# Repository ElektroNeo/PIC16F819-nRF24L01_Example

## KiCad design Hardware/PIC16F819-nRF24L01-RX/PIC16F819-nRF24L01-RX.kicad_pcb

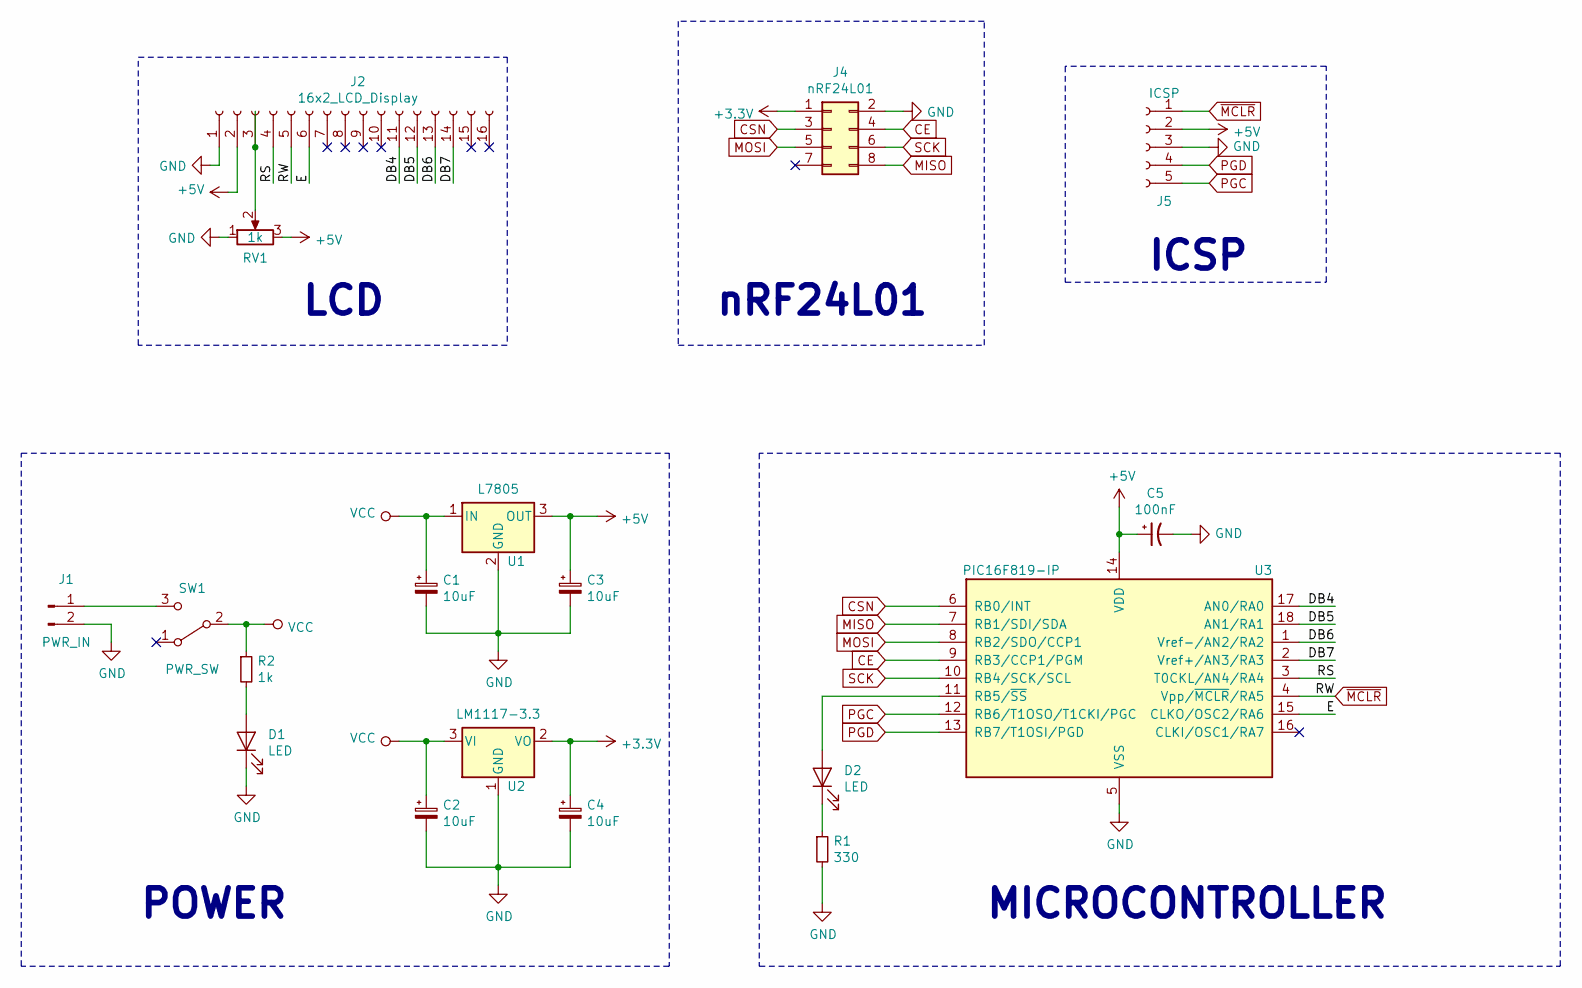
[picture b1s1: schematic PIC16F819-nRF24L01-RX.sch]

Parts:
C1, C2, C3, C4: 10uF; CP_Radial_D8.0mm_P5.00mm
C5: 100nF; C_Disc_D5.0mm_W2.5mm_P5.00mm
D1, D2: LED; LED_D5.0mm
J1: PWR_IN; PinHeader_1x02_P2.54mm_Vertical
J2: 16x2_LCD_Display; PinSocket_1x16_P2.54mm_Vertical
J4: nRF24L01; PinSocket_2x04_P2.54mm_Vertical
J5: ICSP; PinSocket_1x05_P2.54mm_Vertical
R1: 330; R_Axial_DIN0309_L9.0mm_D3.2mm_P5.08mm_Vertical
R2: 1k; R_Axial_DIN0309_L9.0mm_D3.2mm_P5.08mm_Vertical
RV1: 1k; Potentiometer_Vishay_248BH-249BH_Single_Horizontal
SW1: PWR_SW; PinHeader_1x03_P2.54mm_Vertical
U1: L7805; TO-220-3_Vertical
U2: LM1117-3.3; TO-220-3_Vertical
U3: PIC16F819-IP; DIP-18_W7.62mm_LongPads

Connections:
+3V3: C4.1, J4.1, U2.2 (VO)
+5V: C3.1, C5.1, J2.2, J5.2, RV1.3, U1.3 (OUT), U3.14 (VDD)
/DB4: J2.11, U3.17 (AN0/RA0)
/DB5: J2.12, U3.18 (AN1/RA1)
/DB6: J2.13, U3.1 (Vref-/AN2/RA2)
/DB7: J2.14, U3.2 (Vref+/AN3/RA3)
/E: J2.6, U3.15 (CLKO/OSC2/RA6)
/RS: J2.4, U3.3 (T0CKL/AN4/RA4)
CE: J4.4, U3.9 (RB3/CCP1/PGM)
CSN: J4.3, U3.6 (RB0/INT)
GND: C1.2, C2.2, C3.2, C4.2, C5.2, D1.1 (K), J1.2, J2.1, J4.2, J5.3, R1.2, RV1.1, U1.2 (GND), U2.1 (GND), U3.5 (VSS)
MISO: J4.8, U3.7 (RB1/SDI/SDA)
MOSI: J4.5, U3.8 (RB2/SDO/CCP1)
unnamed: D1.2 (A), R2.2
unnamed: D2.1 (K), R1.1
unnamed: D2.2 (A), U3.11 (RB5/~SS~)
unnamed: J1.1, SW1.3 (C)
unnamed: J2.3, RV1.2
PGC: J5.5, U3.12 (RB6/T1OSO/T1CKI/PGC)
PGD: J5.4, U3.13 (RB7/T1OSI/PGD)
SCK: J4.6, U3.10 (RB4/SCK/SCL)
VCC: C1.1, C2.1, R2.1, SW1.2 (B), U1.1 (IN), U2.3 (VI)
~MCLR: J2.5, J5.1, U3.4 (Vpp/~MCLR~/RA5)

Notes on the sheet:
POWER
MICROCONTROLLER
nRF24L01
LCD
ICSP

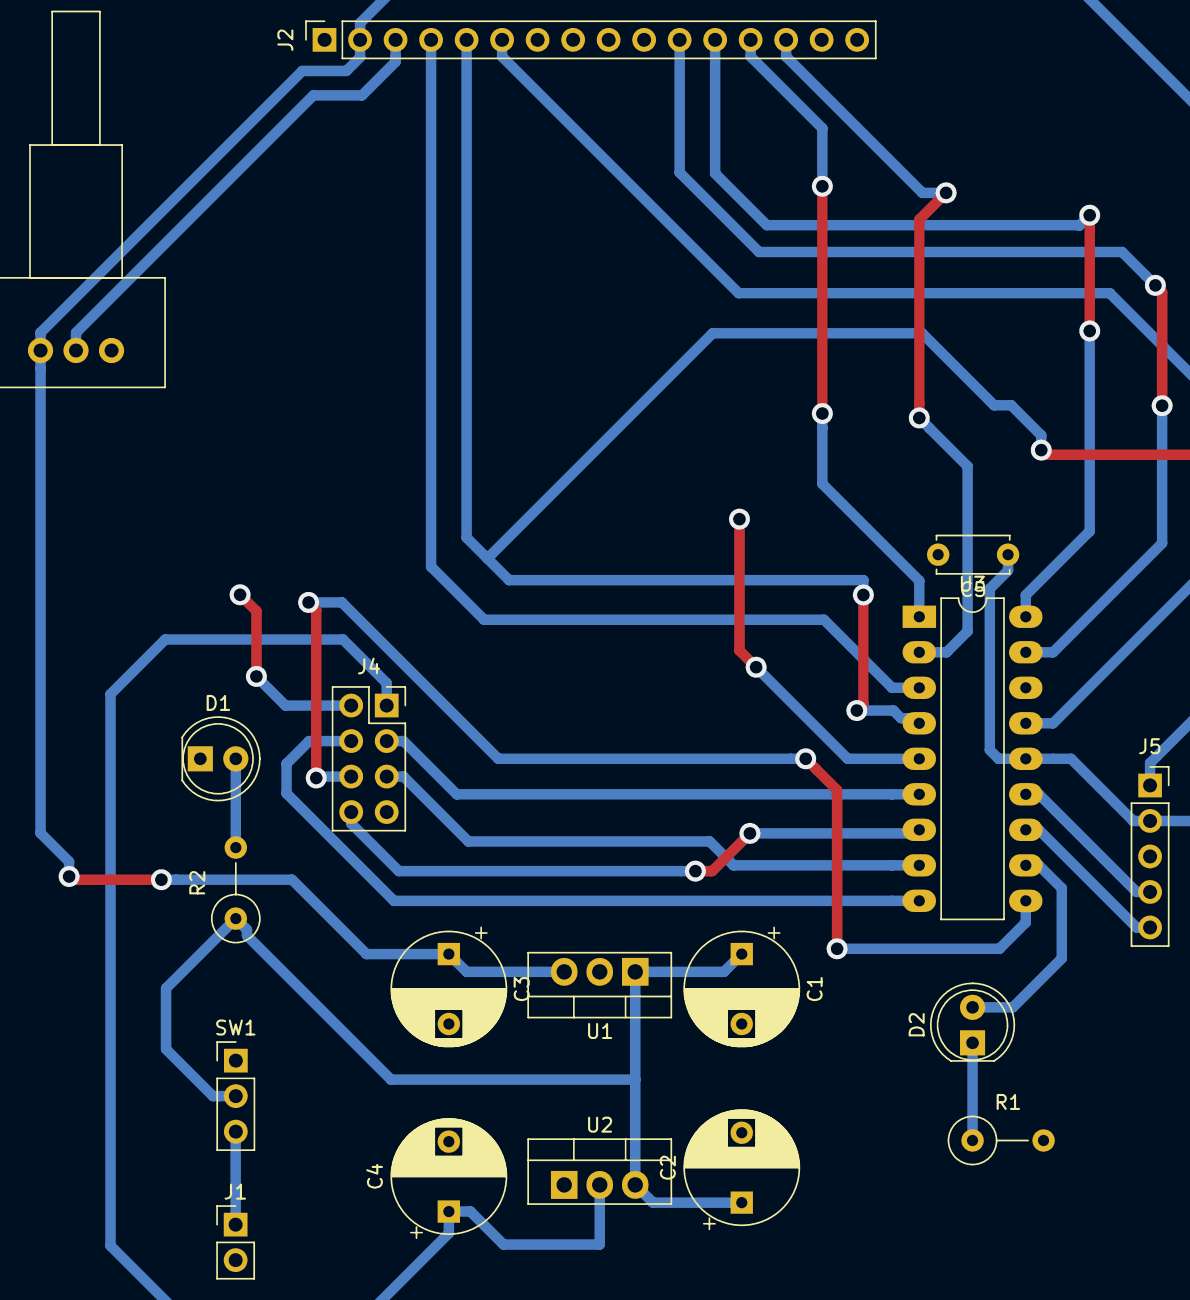
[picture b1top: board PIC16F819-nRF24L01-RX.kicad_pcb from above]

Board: 2 copper layers, 18 parts (0 on the bottom side), 23 nets.

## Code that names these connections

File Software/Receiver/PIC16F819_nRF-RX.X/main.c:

/*
 * File:   main.c
 * Author: bahti
 *
 * Created on May 12, 2019, 4:56 AM
 */

// PIC16F819 Configuration Bit Settings

// 'C' source line config statements

// CONFIG
#pragma config FOSC = INTOSCIO  // Oscillator Selection bits (INTRC oscillator; port I/O function on both RA6/OSC2/CLKO pin and RA7/OSC1/CLKI pin)
#pragma config WDTE = OFF       // Watchdog Timer Enable bit (WDT disabled)
#pragma config PWRTE = OFF      // Power-up Timer Enable bit (PWRT disabled)
#pragma config MCLRE = OFF      // RA5/MCLR/VPP Pin Function Select bit (RA5/MCLR/VPP pin function is digital I/O, MCLR internally tied to VDD)
#pragma config BOREN = ON       // Brown-out Reset Enable bit (BOR enabled)
#pragma config LVP = OFF        // Low-Voltage Programming Enable bit (RB3/PGM pin has digital I/O function, HV on MCLR must be used for programming)
#pragma config CPD = OFF        // Data EE Memory Code Protection bit (Code protection off)
#pragma config WRT = OFF        // Flash Program Memory Write Enable bits (Write protection off)
#pragma config CCPMX = RB2      // CCP1 Pin Selection bit (CCP1 function on RB2)
#pragma config CP = OFF         // Flash Program Memory Code Protection bit (Code protection off)

// #pragma config statements should precede project file includes.
// Use project enums instead of #define for ON and OFF.

#include <stdio.h>
#include <string.h>
#include <xc.h>
#define _XTAL_FREQ 8000000

#include "lcd.h"
#include "nRF24L01.h"

int main ( void ) {
    
    OSCCONbits.IRCF = 0b111;
    OSCCONbits.IOFS = 1;
    
    TRISBbits.TRISB5 = 0;
    PORTBbits.RB5 = 0;

    LCDInitialize();
    nRF_Init(RX_MODE, 0x40);
    
    char bufferRX[32];
    bufferRX[0] = '0';
    
    char str[20] = "Baglanti yok.";
    
    LCDSendByte(0, ClearDisplay);
    LCDPutString(str, 1, 1);
    __delay_ms(2000);
    
    while(1) {
        if(nRF_DataReady()){
            nRF_ReadData(bufferRX);
            
            if(bufferRX[0] == '-') {
                strcpy(str, "Baglandi...");
                PORTBbits.RB5 = 0;
            }else if(bufferRX[0] == 'A') {
                strcpy(str, "A Butonu.");
                __delay_ms(50);
                PORTBbits.RB5 ^= 1;
            }else if(bufferRX[0] == 'B') {
                strcpy(str, "B Butonu.");
                __delay_ms(150);
                PORTBbits.RB5 ^= 1;
            }else if(bufferRX[0] == 'C') {
                strcpy(str, "C Butonu.");
                __delay_ms(250);
                PORTBbits.RB5 ^= 1;
            }
            
            LCDSendByte(0, ClearDisplay);
            LCDPutString(str, 1, 1);
            LCDPutString("Mustafa Duger", 1, 2);
            __delay_ms(300);
        }
    }
    return (0);
}

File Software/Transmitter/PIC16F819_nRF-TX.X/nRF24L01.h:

/* Microchip Technology Inc. and its subsidiaries.  You may use this software 
 * and any derivatives exclusively with Microchip products. 
 * 
 * THIS SOFTWARE IS SUPPLIED BY MICROCHIP "AS IS".  NO WARRANTIES, WHETHER 
 * EXPRESS, IMPLIED OR STATUTORY, APPLY TO THIS SOFTWARE, INCLUDING ANY IMPLIED 
 * WARRANTIES OF NON-INFRINGEMENT, MERCHANTABILITY, AND FITNESS FOR A 
 * PARTICULAR PURPOSE, OR ITS INTERACTION WITH MICROCHIP PRODUCTS, COMBINATION 
 * WITH ANY OTHER PRODUCTS, OR USE IN ANY APPLICATION. 
 *
 * IN NO EVENT WILL MICROCHIP BE LIABLE FOR ANY INDIRECT, SPECIAL, PUNITIVE, 
 * INCIDENTAL OR CONSEQUENTIAL LOSS, DAMAGE, COST OR EXPENSE OF ANY KIND 
 * WHATSOEVER RELATED TO THE SOFTWARE, HOWEVER CAUSED, EVEN IF MICROCHIP HAS 
 * BEEN ADVISED OF THE POSSIBILITY OR THE DAMAGES ARE FORESEEABLE.  TO THE 
 * FULLEST EXTENT ALLOWED BY LAW, MICROCHIP'S TOTAL LIABILITY ON ALL CLAIMS 
 * IN ANY WAY RELATED TO THIS SOFTWARE WILL NOT EXCEED THE AMOUNT OF FEES, IF 
 * ANY, THAT YOU HAVE PAID DIRECTLY TO MICROCHIP FOR THIS SOFTWARE.
 *
 * MICROCHIP PROVIDES THIS SOFTWARE CONDITIONALLY UPON YOUR ACCEPTANCE OF THESE 
 * TERMS. 
 */

/* 
 * File:   
 * Author: Bahtiyar Bayram
 * Comments:
 * Revision history: 
 */

// This is a guard condition so that contents of this file are not included
// more than once.  
#ifndef NRF24L01
#define	NRF24L01

#include <xc.h> // include processor files - each processor file is guarded.  

#ifndef _XTAL_FREQ
#define _XTAL_FREQ 8000000
#endif

#define CE_RF           PORTBbits.RB3
#define CSN_RF          PORTBbits.RB0
#define MOSI_RF         PORTBbits.RB1   // SDI Pin
#define MISO_RF         PORTBbits.RB2   // SDO Pin
#define SCK_RF          PORTBbits.RB4   // SCK Pin

#define CE_RF_DDR       TRISBbits.TRISB3
#define CSN_RF_DDR      TRISBbits.TRISB0
#define MOSI_RF_DDR     TRISBbits.TRISB1
#define MISO_RF_DDR     TRISBbits.TRISB2
#define SCK_RF_DDR      TRISBbits.TRISB4

void nRF_Init(char, char);
void nRF_WriteRegister(char, char);
char nRF_ReadRegister(char);
void SPI_Write(char);
char SPI_Read(void);
void nRF_WriteBuffer(char, char *, char);
void nRF_ReadBuffer(char, char *, char);
void nRF_SetMode(char);
void nRF_Flush(void);
void nRF_SendData(char *);
void nRF_ReadData(char *);
char nRF_DataReady(void);
void nRF_SetChannel(char);
char nRF_GetChannel(void);
void nRF_StandByI(void);


#define PAYLOAD_BYTES       5 // Sets the bytes to send or read.
#define RX_MODE             1
#define TX_MODE             0

//==============================================================================
// Register Map.
//==============================================================================
#define R_REGISTER          0x00  
#define W_REGISTER          0x20  
#define R_RX_PAYLOAD        0x61  
#define W_TX_PAYLOAD        0xA0  
#define FLUSH_TX            0xE1  
#define FLUSH_RX            0xE2  
#define REUSE_TX_PL         0xE3  

#define CONFIG             0x00  
#define EN_AA               0x01  
#define EN_RXADDR           0x02  
#define SETUP_AW            0x03  
#define SETUP_RETR          0x04  
#define RF_CH               0x05  
#define RF_SETUP            0x06  
#define STATUS_N            0x07  
#define OBSERVE_TX          0x08  
#define CD                  0x09  
#define RX_ADDR_P0          0x0A  
#define RX_ADDR_P1          0x0B  
#define RX_ADDR_P2          0x0C  
#define RX_ADDR_P3          0x0D  
#define RX_ADDR_P4          0x0E  
#define RX_ADDR_P5          0x0F  
#define TX_ADDR             0x10  
#define RX_PW_P0            0x11  
#define RX_PW_P1            0x12  
#define RX_PW_P2            0x13  
#define RX_PW_P3            0x14  
#define RX_PW_P4            0x15  
#define RX_PW_P5            0x16  
#define FIFO_STATUS         0x17  

#endif	/* XC_HEADER_TEMPLATE_H */

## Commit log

2019-05-14 Import files.
2019-05-14 Added schematic pdfs.
